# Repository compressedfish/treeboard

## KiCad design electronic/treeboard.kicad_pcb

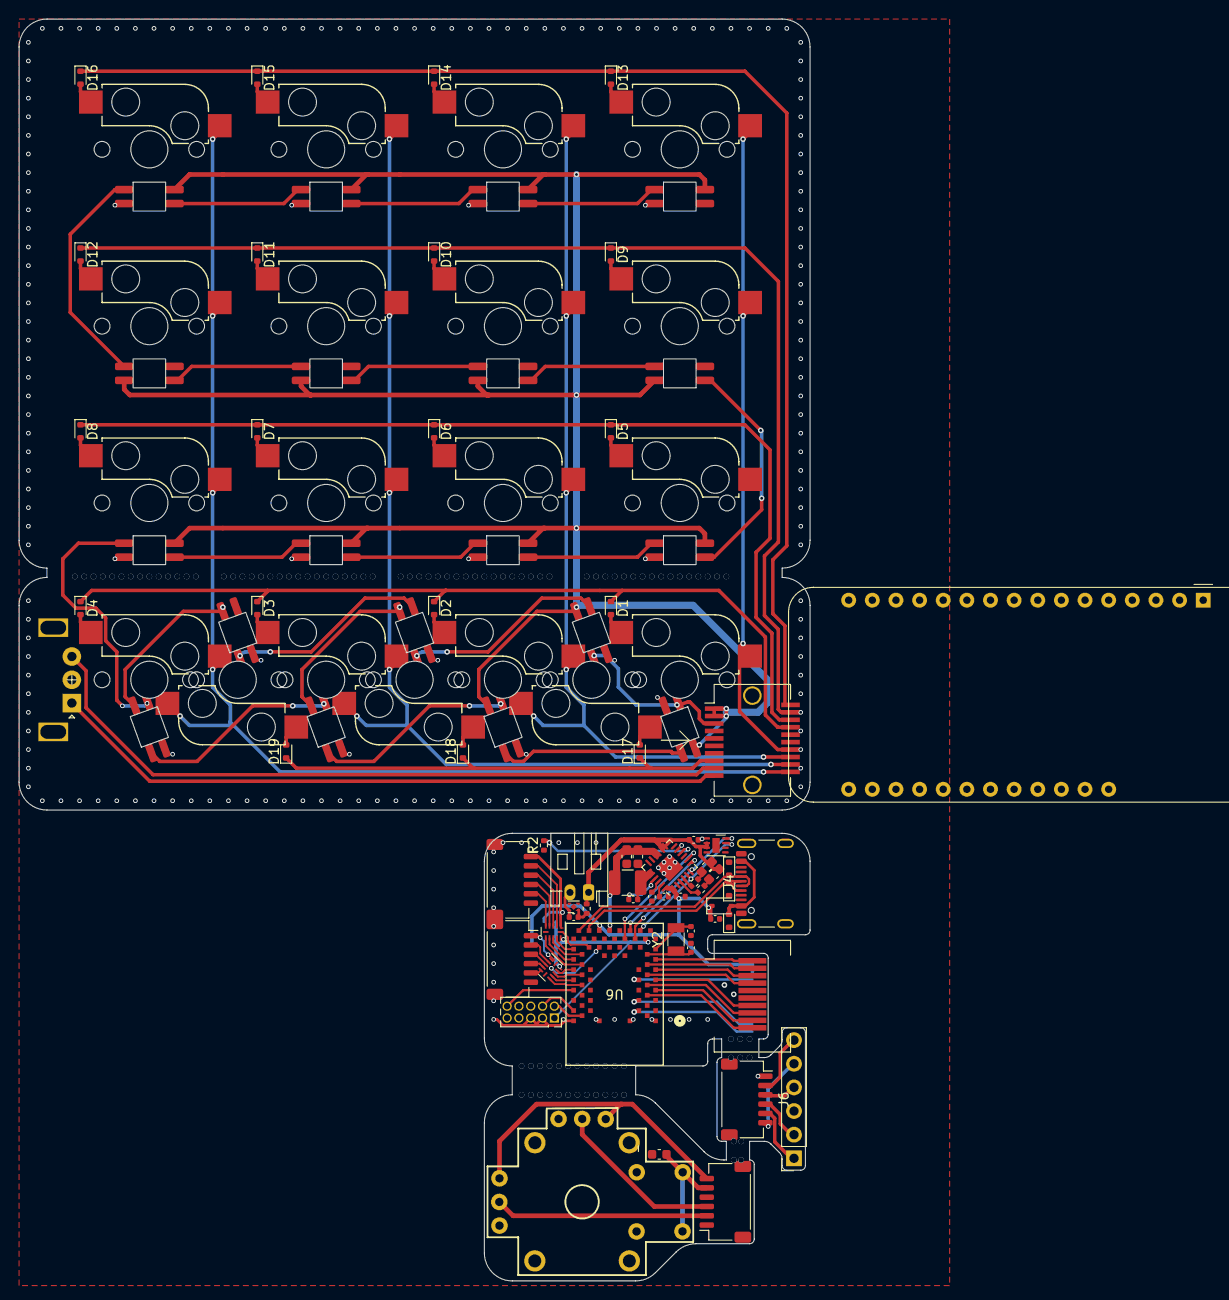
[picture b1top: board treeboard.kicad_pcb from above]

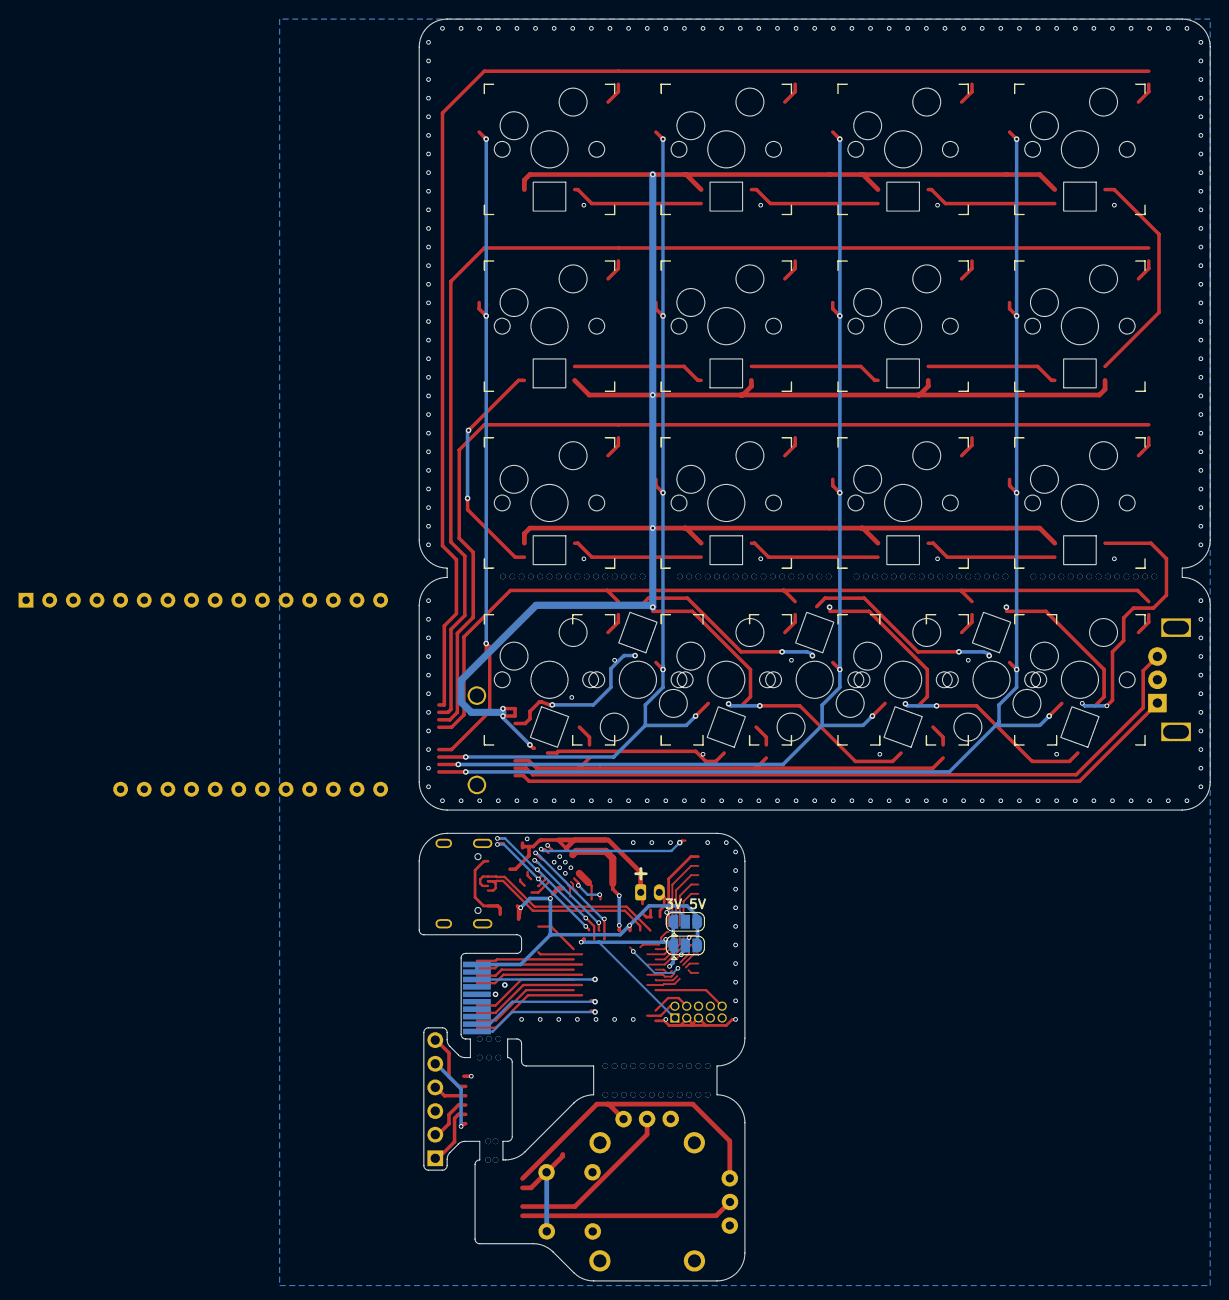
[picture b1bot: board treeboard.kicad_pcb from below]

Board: 4 copper layers, 85.0 x 135.6 mm, 102 parts (21 on the bottom side), 104 nets.

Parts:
A1: Adafruit_Feather_Generic; Adafruit_Feather
BT1: Battery_Cell; JST_PH_S2B-PH-K_1x02_P2.00mm_Horizontal
C1, C9: 1u; C_0402_1005Metric
C3: C; C_0402_1005Metric
C4: 47n; C_0402_1005Metric
C5: 4.7u; C_0402_1005Metric
C6, C7: 10u; C_0603_1608Metric
C8: 8.2u; C_0402_1005Metric
C11: 100n; C_0402_1005Metric
C12: C; C_0603_1608Metric
C31, C32: 12p; C_0402_1005Metric
D1, D2, D3, D4, D5, D6, D7, D8, D9, D10, D11, D12, D13, D14, D15, D16, D17, D18, D19: 1N4148; D_SOD-523
D20, D21, D22, D23, D24, D25, D26, D27, D28, D29, D30, D31, D32, D33, D34, D35, D36, D37, D38: SK6812MINI; SK6812MINI-E
D39: D; D_SOD-323
D40, D41, D42: D_TVS; D_SOD-523
D43, D44: LED_Small; C_0603_1608Metric
J2, J3: Conn_01x06_MountingPin; JST_SH_SM06B-SRSS-TB_1x06-1MP_P1.00mm_Horizontal
J4: USB_C_Receptacle_USB2.0; USB_C_Receptacle_GCT_USB4105-xx-A_16P_TopMnt_Horizontal
J5: Conn_01x06_Socket; PinSocket_1x06_P2.54mm_Vertical
J6, J7: Conn_01x06_Socket; JST_SH_SM06B-SRSS-TB_1x06-1MP_P1.00mm_Horizontal
J8, J12: Conn_02x10_Counter_Clockwise; Connector_SFP_and_Cage
J9: Conn_02x05_Odd_Even; PinSocket_2x05_P1.27mm_Vertical
JP1, JP2: SolderJumper_3_Open; SolderJumper-3_P1.3mm_Open_RoundedPad1.0x1.5mm
L1: 1u; L_1210_3225Metric
R1: 100; R_0402_1005Metric
R2: 1k; R_0402_1005Metric
R4, R5: 2.2k; R_0402_1005Metric
SW1, SW2, SW3, SW4, SW5, SW6, SW7, SW8, SW9, SW10, SW11, SW12, SW13, SW14, SW15, SW16, SW17, SW18, SW19: SW_Push_45deg; Kailh_socket_MX
SW20: RotaryEncoder; encoder
U1, U7: TXB0104RUT; Texas_R-PUQFN-N12
U2: Texas_S-PVQFN-N24_EP2.1x2.1mm
U3: DFN-8-1EP_2x2mm_P0.5mm_EP0.8x1.6mm
U5: PS4_joystick
U6: BMD-340-A-R; BMD-340_UBL
U8: UDFN-4-1EP_1x1mm_P0.65mm_EP0.48x0.48mm
Y2: 32.064kHz; Crystal_SMD_3215-2Pin_3.2x1.5mm

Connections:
+3V3: J9.1, JP1.1 (A), JP2.1 (A), U1.11 (VCCB), U6.17 (VCC), U7.11 (VCCB)
+5V: C3.1, C9.1, D20.4 (VDD), D21.4 (VDD), D22.4 (VDD), D23.4 (VDD), D24.4 (VDD), D25.4 (VDD), D26.4 (VDD), D27.4 (VDD), D28.4 (VDD), D29.4 (VDD), D30.4 (VDD), D31.4 (VDD), D32.4 (VDD), D33.4 (VDD), D34.4 (VDD), D35.4 (VDD), D36.4 (VDD), D37.4 (VDD), D38.4 (VDD), D39.1 (K), J8.1, J8.2, J12.1, J12.2, JP1.3 (B), JP2.3 (B), U2.1 (VBUS), U2.24 (VBUS), U6.66 (VBUS)
/CLK: J5.2, J6.4
/CS: J5.6, J6.2
/D+: D40.2 (A2), J4.A6 (D+), J4.B6 (D+), U6.68 (USB-D+)
/D-: D41.2 (A2), J4.A7 (D-), J4.B7 (D-), U6.67 (USB-D-)
/DIN: J5.1, J6.5
/DOUT: J5.4, J6.3
BAT: BT1.1 (+), C11.1, D43.2 (A), D44.2 (A), R1.1, U2.13 (BAT), U2.14 (BAT), U3.2 (VDD), U3.3 (VDD)
COL0: J8.14, J12.14, SW1.2, SW5.2, SW9.2, SW13.2, U6.9 (P0.28)
COL1: J8.13, J12.13, SW2.2, SW6.2, SW10.2, SW14.2, SW17.2, U6.8 (P0.27)
COL2: J8.12, J12.12, SW3.2, SW7.2, SW11.2, SW15.2, SW18.2, U6.7 (P0.26)
COL3: J8.11, J12.11, SW4.2, SW8.2, SW12.2, SW16.2, SW19.2, U6.6 (P0.25)
ENC_A: J8.10, J12.10, SW20.A, U6.48 (P1.05)
ENC_B: J8.9, J12.9, SW20.B, U6.49 (P1.06)
GND: C3.2, C5.2, C6.2, C7.2, C8.2, C9.2, C11.2, C12.2, C31.1, C32.1, D20.2 (VSS), D21.2 (VSS), D22.2 (VSS), D23.2 (VSS), D24.2 (VSS), D25.2 (VSS), D26.2 (VSS), D27.2 (VSS), D28.2 (VSS), D29.2 (VSS), D30.2 (VSS), D31.2 (VSS), D32.2 (VSS), D33.2 (VSS), D34.2 (VSS), D35.2 (VSS), D36.2 (VSS), D37.2 (VSS), D38.2 (VSS), D40.1 (A1), D41.1 (A1), D42.1 (A1), J2.6, J2.MP (MountPin), J3.6, J3.MP (MountPin), J4.A1 (GND), J4.A12 (GND), J4.B1 (GND), J4.B12 (GND), J4.S1 (SHIELD), J5.3, J6.1, J6.MP, J7.1, J8.4, J8.5, J8.6, J8.7, J8.15, J8.16, J9.3, J9.5, J12.4, J12.5, J12.6, J12.7, J12.15, J12.16, R2.1, SW20.C, U1.6 (GND), U2.2 (PSEL), U2.9 (~CE), U2.17 (PGND), U2.18 (PGND), U3.1 (GND), U3.4 (GND), U3.9 (GND), U5.B2A (SEL-), U5.B2B (SEL-), U5.H3 (H-), U5.V3 (V-), U6.1 (GND), U6.2 (GND), U6.3 (GND), U6.4 (GND), U6.5 (GND), U6.16 (GND), U6.18 (GND), U6.29 (GND), U6.30 (GND), U6.45 (GND), U6.46 (GND), U6.47 (GND), U6.55 (GND), U7.6 (GND), U8.2 (VSS), U8.3 (VSS), U8.5 (VSS)
INT: U2.7 (INT), U6.63 (P1.14)
unnamed: BT1.2 (-), C1.2, U8.4 (BAT-)
unnamed: D1.2 (A), SW1.1
unnamed: D2.2 (A), SW2.1
unnamed: D3.2 (A), SW3.1
unnamed: D4.2 (A), SW4.1
unnamed: D5.2 (A), SW5.1
unnamed: D6.2 (A), SW6.1
unnamed: D7.2 (A), SW7.1
unnamed: D8.2 (A), SW8.1
unnamed: D9.2 (A), SW9.1
unnamed: D10.2 (A), SW10.1
unnamed: D11.2 (A), SW11.1
unnamed: D12.2 (A), SW12.1
unnamed: D13.2 (A), SW13.1
unnamed: D14.2 (A), SW14.1
unnamed: D15.2 (A), SW15.1
unnamed: D16.2 (A), SW16.1
unnamed: D17.2 (A), SW17.1
unnamed: D18.2 (A), SW18.1
unnamed: D19.2 (A), SW19.1
unnamed: D20.1 (DOUT), D21.3 (DIN)
unnamed: D21.1 (DOUT), D22.3 (DIN)
unnamed: D23.1 (DOUT), D24.3 (DIN)
unnamed: D24.1 (DOUT), D25.3 (DIN)
unnamed: D25.1 (DOUT), D26.3 (DIN)
unnamed: D26.1 (DOUT), D30.3 (DIN)
unnamed: D27.3 (DIN), D28.1 (DOUT)
unnamed: D27.1 (DOUT), D31.3 (DIN)
unnamed: D28.3 (DIN), D29.1 (DOUT)
unnamed: D29.3 (DIN), D30.1 (DOUT)
unnamed: D31.1 (DOUT), D32.3 (DIN)
unnamed: D32.1 (DOUT), D33.3 (DIN)
unnamed: D33.1 (DOUT), D34.3 (DIN)
unnamed: D34.1 (DOUT), D38.3 (DIN)
unnamed: D35.3 (DIN), D36.1 (DOUT)
unnamed: D36.3 (DIN), D37.1 (DOUT)
unnamed: D37.3 (DIN), D38.1 (DOUT)
unnamed: D39.2 (A), D42.2 (A2), J4.A4 (VBUS), J4.A9 (VBUS), J4.B4 (VBUS), J4.B9 (VBUS)
unnamed: D43.1 (K), R4.2
unnamed: D44.1 (K), R5.2
unnamed: J2.1, JP1.2 (C), U1.1 (VCCA)
unnamed: J2.2, U1.2 (A1)
unnamed: J2.3, U1.3 (A2)
unnamed: J2.4, U1.4 (A3)
unnamed: J2.5, U1.5 (A4)
unnamed: J3.1, JP2.2 (C), U7.1 (VCCA)
unnamed: J3.2, U7.2 (A1)
unnamed: J3.3, U7.3 (A2)
unnamed: J3.4, U7.4 (A3)
unnamed: J3.5, U7.5 (A4)
unnamed: J7.2, U5.H2 (H)
unnamed: J7.3, U5.V2 (V)
unnamed: C12.1, J7.5, U5.B1A (SEL+), U5.B1B (SEL+)
unnamed: J7.6, U5.H1 (H+), U5.V1 (V+)
unnamed: C4.2, U2.21 (BTST)
unnamed: R2.2, U2.10 (ILIM)
unnamed: C8.1, U2.23 (PMID)
unnamed: C5.1, U2.22 (REGN)
unnamed: R5.1, U2.4 (STAT)
unnamed: R4.1, U2.3 (~PG)
unnamed: C32.2, U6.14 (P0.01), Y2.2
unnamed: C31.2, U6.15 (P0.02), Y2.1
unnamed: C1.1, R1.2, U8.1 (BAT+)
OTG: U2.8 (OTG), U6.21 (P0.05)
P0_0: U1.10 (B1), U6.35 (P0.17)
P0_1: U1.9 (B2), U6.36 (P0.21)
P0_2: U1.8 (B3), U6.37 (P0.19)
P0_3: U1.7 (B4), U6.38 (P0.20)
P0_EN: U1.12 (OE), U6.26 (P0.10)
P1_0: U6.31 (P0.13), U7.10 (B1)
P1_1: U6.32 (P0.14), U7.9 (B2)
P1_2: U6.33 (P0.15), U7.8 (B3)
P1_3: U6.34 (P0.16), U7.7 (B4)
P1_EN: U6.28 (P0.12), U7.12 (OE)
RGB_CTRL: D20.3 (DIN), D23.3 (DIN), J8.3, J12.3, U6.51 (P1.08)
ROW0: D1.1 (K), D2.1 (K), D3.1 (K), D4.1 (K), J8.17, J12.17, U6.10 (P0.29)
ROW1: D5.1 (K), D6.1 (K), D7.1 (K), D8.1 (K), J8.18, J12.18, U6.11 (P0.30)
ROW2: D9.1 (K), D10.1 (K), D11.1 (K), D12.1 (K), J8.19, J12.19, U6.12 (P0.31)
ROW3: D13.1 (K), D14.1 (K), D15.1 (K), D16.1 (K), J8.20, J12.20, U6.13 (P0.00)
ROW4: D17.1 (K), D18.1 (K), D19.1 (K), J8.8, J12.8
SCL: U2.5 (SCL), U3.7 (SCL), U6.62 (P1.13)
SDA: U2.6 (SDA), U3.8 (SDA), U6.19 (P0.03)
SW: C4.1, L1.1, U2.19 (SW), U2.20 (SW)
SWCLK: J9.4, U6.43 (SWCLK)
SWDIO: J9.2, U6.44 (SWDIO)
VCC: C6.1, C7.1, J5.5, J6.6, L1.2, U2.15 (SYS), U2.16 (SYS), U6.65 (VCCH)
nRESET: J9.10, U6.39 (P0.18)

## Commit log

2024-10-08 initialising
    putting the existing stuff up
2025-02-03 backup before switch
    switching to nrf52840 feather
